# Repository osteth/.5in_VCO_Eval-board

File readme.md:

Bill of materials
4x JOHNSON  part#142-0701-801  RF / Coaxial Connector, SMA Coaxial, Straight Jack, Solder, 50 ohm, Beryllium Copper

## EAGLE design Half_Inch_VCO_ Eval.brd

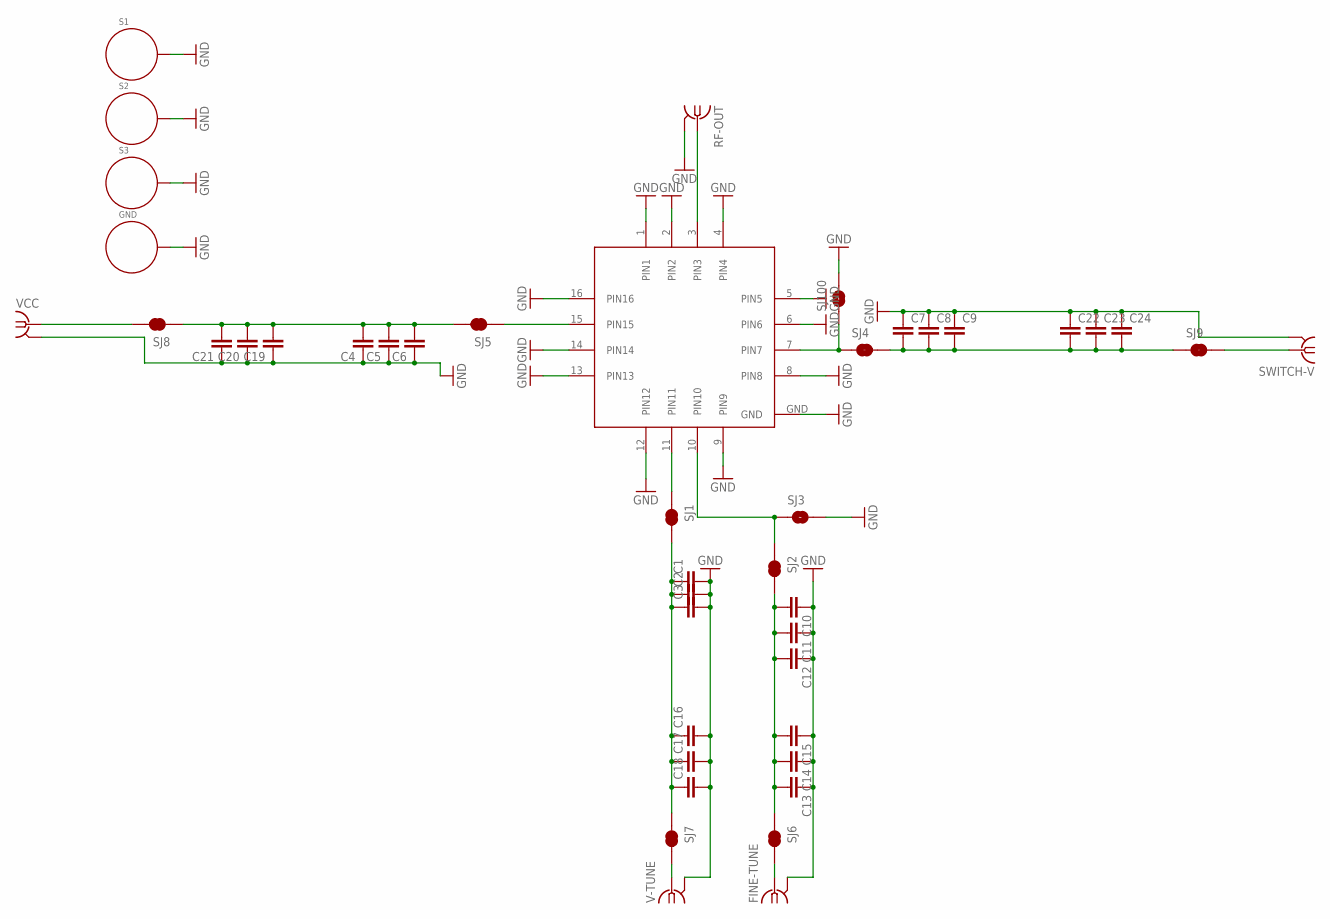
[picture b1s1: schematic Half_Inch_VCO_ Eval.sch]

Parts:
C1, C2, C3, C4, C5, C6, C7, C8, C9, C10, C11, C12, C13, C14, C15, C16, C17, C18, C19, C20, C21, C22, C23, C24: CAP0402-CAP; 0402-CAP
FINE-TUNE: SMA-142-0701-801/806; J502-ND-142-0701-801/806
GND: STANDOFF_ELECTRICAL; STANDOFF-ELECTRICAL
RF-OUT: SMA-142-0701-871/876; J502-ND-142-0701-871/876
S1, S2, S3: STANDOFF_ELECTRICAL; STANDOFF-ELECTRICAL
SJ1, SJ2, SJ4, SJ5, SJ6, SJ7, SJ8, SJ9: JUMPER-PAD-2-NC_BY_TRACE; PAD-JUMPER-2-NC_BY_TRACE_YES_SILK
SJ3, SJ100: SOLDERJUMPER-OLDNC2; SJ_2S-NOTRACE
SWITCH-V: SMA-142-0701-801/806; J502-ND-142-0701-801/806
U$1: RFVC6406
V-TUNE: SMA-142-0701-801/806; J502-ND-142-0701-801/806
VCC: SMA-142-0701-801/806; J502-ND-142-0701-801/806

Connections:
GND: C1.2, C2.2, C3.2, C4.1, C5.1, C6.1, C7.1, C8.1, C9.1, C10.1, C11.1, C12.1, C13.1, C14.1, C15.1, C16.2, C17.2, C18.2, C19.1, C20.1, C21.1, C22.1, C23.1, C24.1, FINE-TUNE.G@1 (2), FINE-TUNE.G@2 (2), FINE-TUNE.G@3 (2), FINE-TUNE.G@4 (2), GND.P1, RF-OUT.G@1 (2), RF-OUT.G@2 (2), RF-OUT.G@3 (2), RF-OUT.G@4 (2), S1.P1, S2.P1, S3.P1, SJ3.2, SJ100.2, SWITCH-V.G@1 (2), SWITCH-V.G@2 (2), SWITCH-V.G@3 (2), SWITCH-V.G@4 (2), U$1.1 (PIN1), U$1.2 (PIN2), U$1.4 (PIN4), U$1.5 (PIN5), U$1.6 (PIN6), U$1.8 (PIN8), U$1.9 (PIN9), U$1.12 (PIN12), U$1.13 (PIN13), U$1.14 (PIN14), U$1.16 (PIN16), U$1.GND, V-TUNE.G@1 (2), V-TUNE.G@2 (2), V-TUNE.G@3 (2), V-TUNE.G@4 (2), VCC.G@1 (2), VCC.G@2 (2), VCC.G@3 (2), VCC.G@4 (2)
unnamed: SJ8.2, VCC.1
unnamed: RF-OUT.1, U$1.3 (PIN3)
unnamed: C4.2, C5.2, C6.2, C19.2, C20.2, C21.2, SJ5.2, SJ8.1
unnamed: SJ5.1, U$1.15 (PIN15)
unnamed: FINE-TUNE.1, SJ6.2
unnamed: SJ4.1, SJ100.1, U$1.7 (PIN7)
unnamed: C7.2, C8.2, C9.2, C22.2, C23.2, C24.2, SJ4.2, SJ9.1
unnamed: SJ9.2, SWITCH-V.1
unnamed: SJ1.1, U$1.11 (PIN11)
unnamed: C1.1, C2.1, C3.1, C16.1, C17.1, C18.1, SJ1.2, SJ7.1
unnamed: SJ7.2, V-TUNE.1
unnamed: C10.2, C11.2, C12.2, C13.2, C14.2, C15.2, SJ2.2, SJ6.1
unnamed: SJ2.1, SJ3.1, U$1.10 (PIN10)

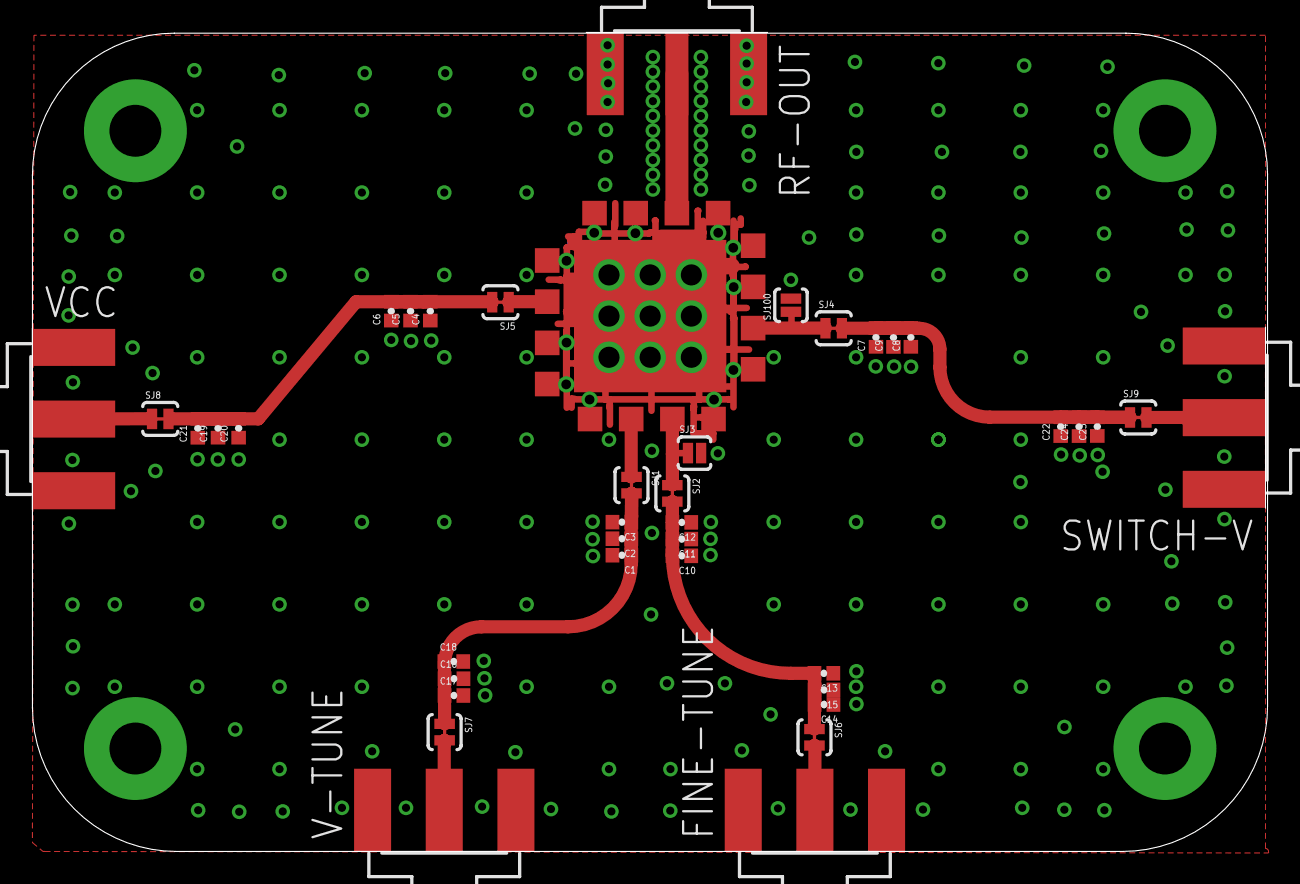
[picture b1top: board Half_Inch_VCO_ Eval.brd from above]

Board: 2 copper layers, 76.2 x 50.5 mm, 44 parts (0 on the bottom side), 14 nets.

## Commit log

2016-08-12 :lollipop: Added .gitattributes & .gitignore files
2016-08-12 initial commit
    uploaded initial design package

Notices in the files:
parts and their libraries:
SparkFun-Capacitors: Licensing: Creative Commons ShareAlike 4.0 International - https://creativecommons.org/licenses/by-sa/4.0
